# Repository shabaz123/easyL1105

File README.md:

# easyL1105 - What is it?
This repository contains resources for working with Texas Instruments MSPM0 microcontrollers, and in particular, the MSPM0L1105 microcontroller.
KiCad files, and Gerber files are present for building a simple development board, called easyL1105. 

The repository also contains Gerber files for a smaller miniL1105 board:

There is also an example starter project, which can be built with Keil or GCC.

# Circuit Diagrams
## easyL1105

## miniL1105

## Note for old Rev 1 Boards
The Rev 1 boards had a known bug; they were missing a 47k pull-up resistor from the *RST pin (pin 6 on the microcontroller) to +3.3V. The newer Rev 2 boards do not have this issue.

If you have a Rev 1 board, the fix is easy, it is possible to patch a resistor onto the underside of the PCB, using an 0805 sized resistor and a short length of 30 AWG Kynar wire.

The easyL1105 Rev 1 board allocates pins PA17(TXD) and PA18(RXD) for UART0, but since PA18(RXD) also has a BOOT function for enabling bootloader mode, there is the unfortunate situation that if the "BSL/UART0" board jumpers are configured to direct UART0 to the USB-UART chip, the pin is in BOOT mode during reset. One workaround for now is to not fit the rightmost jumper (rightmost when the "EasyL1105" and "BSL/UART0" text is the correct way up) during board reboot or power-up, and then fit it later. The better fix is in Rev 2, where a different GPIO pin (PA9) is used in place of PA18(RXD), so that it doesn't clash with the BOOT function

# easyL1105 Parts List
NOTE: The parts lists in this repository are for the Rev 1 board. They need to be updated for Rev 2. However, it is easy to read off the schematic what parts are required. 

| REF                | QTY | VALUE             | DESCRIPTION                                       |
| ------------------ | --- | ----------------- | ------------------------------------------------- |
| C1                 | 1   | 0.47u             | Tant Cap Case A example: T491A474M025AT           |
| C2, C5             | 2   | 10n               | 0805 MLCC Capacitor                               |
| C3,C6,C7           | 3   | 100n              | 0805 MLCC Capacitor                               |
| C4,C8,C9           | 3   | 10u 16V           | Tant Cap Case B example: TAJB106K016RNJ           |
| D1                 | 1   | GREEN             | LED GREEN 0603                                    |
| D2                 | 1   | BLUE              | LED BLUE 0603                                     |
| D3                 | 1   | 1N4001W           | Diode SOD-123                                     |
| D4                 | 1   | PWR               | LED RED 0603                                      |
| J1, J2, J5, J6, J7 | 1   | Header SIL        | Pin Header 2.54mm SIL 40-way (snapped to fit)     |
| J3                 | 1   | 2x5 DIL           | Pin Header 2.54mm DIL 10-way (2x5 way)            |
| J4                 | 1   | USB4085           | Socket GCT USB4805 / XUNPU USB-B10-BRW            |
| R1                 | 1   | 100k 0.1%         | 0805 Resistor 0.1%                                |
| R2,R3,R12          | 3   | 100R              | 0805 Resistor                                     |
| R4,R5,R7           | 3   | 100k              | 0805 Resistor                                     |
| R8,R9,R16          | 3   | 10k               | 0805 Resistor                                     |
| R10                | 1   | 220R              | 0805 Resistor                                     |
| R11                | 1   | 820R              | 0805 Resistor                                     |
| R19                | 1   | 1k                | 0805 Resistor                                     |
| R13                | 1   | 1M                | 0805 Resistor                                     |
| R14,R15            | 2   | 5.1k              | 0805 Resistor                                     |
| SW1, 2, 3          | 3   | Tact Switch       | Tact Button 4x3mm GCT SWT0110                     |
| U1                 | 1   | MSPM0L1105TDGS28R | TI MSPM0 L1105 VSSOP28 DGS                        |
| U2                 | 1   | CH340K            | WCH USB UART IC SSOP-10-1EP                       |
| U3                 | 1   | SRV05-4           | ESD Diode Array SOT23-6                           |
| U4                 | 1   | MIC5209-3.3YS     | LDO 3.3V SOT-223                                  |
| RFIX1              | 1   | 47k               | 0805 Resistor, patched between \*RST and 3.3V     |
| n/a                | 5   | Shorting Jumpers  | Jumpers 2-pin 2.54mm (Red, Black, Green x2, Blue) |

# Example Project
Go into the [**MyStarterProject**](https://github.com/shabaz123/easyL1105/tree/main/MyStarterProject) folder to see an example project called **app_L1105** (and if you plan to use GCC on Linux, then you need the **set_env.sh** file that is also in the MyStarterProject folder; save it to any convenient location). 

Go into the [**app_L1105**](https://github.com/shabaz123/easyL1105/tree/main/MyStarterProject/app_L1105) folder within MyStarterProject, and you'll find README notes explaining how to set up your PC and how to build the code.

If you were creating your own app based on the starter code, then rename the folder MyStarterProject to whatever name you want (for instance, MyLEDProject), and within there, retain the app_L1105 folder name (otherwise, you'd have to modify the contents of IDE files or makefiles). Then, edit the main.c file to do whatever you wish.

# Uploading your Application Firmware to the Microcontroller
Once you have built the example project, you'll want to upload it into the microcontroller. The easyL1105 board has a built-in USB-to-UART adapter. The miniL1105 board will require an external 3.3V logic level USB-UART adapter.

## Set Board Jumpers and Plug into PC
If you're using the easyL1105 board, ensure that two jumpers (green in the photo below) are fitted to direct the USB-UART to **BSL**, and not to UART0. Ensure that the PWR and GND jumpers are fitted (red and black in the photo below).

Attach the board using the USB cable to your PC, and check what port number is associated with it (for example, it may be a number like COM7 if you're using a Windows PC). If you don't see any port, then there may be a fault with the USB-UART circuitry, or an issue with the USB cable perhaps.

## Install and Run UniFlash
Download and install TI UniFlash. Run it, and at the top-right, set **Setting:Manual**. Next, under **Device**, click on **Category:MSP** and then type **MSPM0L110x** and you'll see a selection titled **MSPM0L110X(BOOTLOADER) Serial**. Click to select that.

Next, click on **Start**. 

You'll see a set of boxes appear. Click the empty text entry box to the right of **Application Image 1** and in the file browser that appears, browse to your built firmware file, which will have a **.hex** suffix, for instance, **app_L1105.hex**.

**Don't** press the Load Image button that appears just yet!

Instead, scroll further down, and you'll see a random COM port selected. In that box, type the correct COM port.

## Set Board to Bootloader Mode
Hold down the **BOOT** button on the board, press and release the **RESET** button, then release the **BOOT** button.

## Upload the Firmware
Now you can go back to the **Load Image** button in UniFlash, and press it.

Initially it may take a few seconds (or longer), but eventually you should see output like the following:

```
[21/08/2025, 23:56:17] [INFO] CORTEX_M0P: MSPM0L110x(Bootloader)
[21/08/2025, 23:56:17] [INFO] CORTEX_M0P: Invoking Bootloader....
[21/08/2025, 23:56:18] [ERROR] CORTEX_M0P: Automatic Bootloader invocation failed with response....1
[21/08/2025, 23:56:18] [ERROR] CORTEX_M0P: Try manual Bootloader Invocation...
[21/08/2025, 23:56:19] [INFO] CORTEX_M0P:
[21/08/2025, 23:56:19] [INFO] CORTEX_M0P: BSL Connected
[21/08/2025, 23:56:19] [INFO] CORTEX_M0P: Command Interpreter version: [0x0100] Build ID: [0x0100] Application version: [0x00000000] Active Plugin Interface version: [0x0001] BSL Max buffer size: [0x06C0] BSL Buffer Start address: [0x20000160] BCR Config ID: [0x00000x0001] BSL Config ID [0x00000x0001]
[21/08/2025, 23:56:19] [INFO] CORTEX_M0P: [80] [01] [00] [19] [B2] [B8] [96] [49]
[21/08/2025, 23:56:19] [INFO] CORTEX_M0P: {00}{08} {19} {00} {31} {00} {01} {00} {01} {00} {00} {00} {00} {01} {00} {C0} {06} {60} {01} {00} {20} {01} {00} {00} {00} {01} {00} {00} {00} {49} {61} {57} {8C}
[21/08/2025, 23:56:19] [INFO] CORTEX_M0P: BSL Password is correct!
[21/08/2025, 23:56:19] [INFO] CORTEX_M0P: [80] [21] [00] [21] [FF] [FF] [FF] [FF] [FF] [FF] [FF] [FF] [FF] [FF] [FF] [FF] [FF] [FF] [FF] [FF] [FF] [FF] [FF] [FF] [FF] [FF] [FF] [FF] [FF] [FF] [FF] [FF] [FF] [FF] [FF] [FF] [02] [AA] [F0] [3D]
[21/08/2025, 23:56:19] [INFO] CORTEX_M0P: {00}{08} {02} {00} {3B} {00} {38} {02} {94} {82}
[21/08/2025, 23:56:19] [INFO] CORTEX_M0P: Erasing sectors containing DataBlock starting at 0x0 is successful!
[21/08/2025, 23:56:19] [INFO] CORTEX_M0P: [80] [09] [00] [23] [00] [00] [00] [00] [8F] [02] [00] [00] [34] [27] [34] [14]
[21/08/2025, 23:56:19] [INFO] CORTEX_M0P: {00}{08} {02} {00} {3B} {00} {38} {02} {94} {82}
[21/08/2025, 23:56:19] [INFO] CORTEX_M0P: Erasing memory time elapsed: 0.03107s
[21/08/2025, 23:56:20] [INFO] CORTEX_M0P: [80] [95] [02] [20] [00] [00] [00] [00] [00] [10] [00] [20] [4D] [01] [00] [00] [51] [01] [00] [00] [53] [01] [00] [00] [00] [00] [00] [00] [00] [00] [00] [00] [00] [00] [00] [00] [00] [00] [00] [00] [00] [00] [00] [00] [00] [00] [00] [00] [00] [00] [00] [00] [55] [01] [00] [00] [00] [00] [00] [00] [00] [00] [00] [00] [57] [01] [00] [00] [59] [01] [00] [00] [5B] [01] [00] [00] [5B] [01] [00] [00] [5B] [01] [00] [00] [00] [00] [00] [00] [5B] [01] [00] [00] [00] [00] [00] [00] [00] [00] [00] [00] [00] [00] [00] [00] [00] [00] [00] [00] [5B] [01] [00] [00] [00] [00] [00] [00] [00] [00] [00] [00] [00] [00] [00] [00] [5B] [01] [00] [00] [00] [00] [00] [00] [5B] [01] [00] [00] [5B] [01] [00] [00] [00] [00] [00] [00] [5B] [01] [00] [00] [00] [00] [00] [00] [5B] [01] [00] [00] [00] [00] [00] [00] [00] [00] [00] [00] [00] [00] [00] [00] [5B] [01] [00] [00] [00] [00] [00] [00] [00] [00] [00] [00] [00] [00] [00] [00] [00] [00] [00] [00] [00] [00] [00] [00] [00] [00] [00] [00] [5B] [01] [00] [00] [00] [F0] [02] [F8] [00] [F0] [32] [F8] [0C] [A0] [30] [C8] [08] [38] [24] [18] [2D] [18] [67] [1E] [A2] [46] [AB] [46] [54] [46] [5D] [46] [AC] [42] [01] [D1] [00] [F0] [24] [F8] [7E] [46] [0F] [3E] [B6] [46] [0F] [CC] [01] [26] [33] [42] [00] [D0] [FB] [1A] [33] [43] [A2] [46] [AB] [46] [18] [47] [74] [01] [00] [00] [94] [01] [00] [00] [00] [00] [00] [00] [00] [23] [00] [24] [00] [25] [00] [26] [10] [3A] [01] [D3] [78] [C1] [FB] [D8] [52] [07] [00] [D3] [30] [C1] [00] [D5] [0B] [60] [70] [47] [1F] [B5] [1F] [BD] [10] [B5] [10] [BD] [00] [F0] [27] [F8] [11] [46] [FF] [F7] [F7] [FF] [00] [F0] [59] [F8] [00] [F0] [3F] [F8] [03] [B4] [FF] [F7] [F2] [FF] [03] [BC] [00] [F0] [45] [F8] [00] [00] [06] [48] [00] [47] [FE] [E7] [FE] [E7] [FE] [E7] [FE] [E7] [FE] [E7] [FE] [E7] [03] [48] [04] [49] [02] [4A] [04] [4B] [70] [47] [00] [00] [C1] [00] [00] [00] [60] [00] [00] [20] [00] [10] [00] [20] [00] [0C] [00] [20] [70] [47] [70] [47] [70] [47] [75] [46] [00] [F0] [24] [F8] [AE] [46] [05] [00] [69] [46] [53] [46] [C0] [08] [C0] [00] [85] [46] [18] [B0] [20] [B5] [FF] [F7] [E1] [FF] [60] [BC] [B6] [46] [00] [26] [00] [27] [C0] [C5] [C0] [C5] [C0] [C5] [C0] [C5] [C0] [C5] [C0] [C5] [C0] [C5] [C0] [C5] [40] [3D] [49] [08] [49] [00] [8D] [46] [70] [47] [10] [B5] [04] [46] [C0] [46] [C0] [46] [20] [46] [FF] [F7] [BA] [FF] [10] [BD] [00] [48] [70] [47] [00] [00] [00] [20] [01] [49] [18] [20] [AB] [BE] [FE] [E7] [26] [00] [02] [00] [70] [47] [81] [1E] [09] [1F] [00] [BF] [FC] [D2] [70] [47] [82] [B0] [1A] [48] [1A] [49] [41] [60] [1A] [49] [01] [60] [10] [20] [FF] [F7] [F2] [FF] [19] [48] [81] [21] [01] [60] [01] [20] [80] [06] [17] [49] [08] [60] [08] [63] [7D] [22] [92] [01] [0B] [46] [20] [3B] [18] [60] [00] [23] [1C] [46] [02] [E0] [64] [1C] [64] [2C] [08] [D0] [00] [93] [00] [9D] [95] [42] [F8] [D2] [00] [BF] [00] [9D] [6D] [1C] [00] [95] [F7] [E7] [08] [60] [00] [23] [1C] [46] [02] [E0] [64] [1C] [64] [2C] [E6] [D0] [01] [93] [01] [9D] [95] [42] [F8] [D2] [00] [BF] [01] [9D] [6D] [1C] [01] [95] [F7] [E7] [C0] [46] [00] [08] [0A] [40] [03] [00] [00] [B1] [01] [00] [00] [26] [6C] [80] [42] [40] [A0] [12] [0A] [40] [00] [00] [00] [00] [90] [02] [00] [00] [00] [00] [00] [20] [60] [00] [00] [00] [08] [01] [00] [00] [90] [02] [00] [00] [00] [0C] [00] [20] [00] [04] [00] [00] [08] [01] [00] [00] [5D] [8C] [43] [C0]
[21/08/2025, 23:56:20] [INFO] CORTEX_M0P: {00}{08} {02} {00} {3B} {00} {38} {02} {94} {82}
[21/08/2025, 23:56:20] [INFO] CORTEX_M0P: Programming memory time elapsed: 0.7061s
[21/08/2025, 23:56:20] [INFO] CORTEX_M0P: Number of bytes programmed: 656 bytes
[21/08/2025, 23:56:20] [INFO] CORTEX_M0P: Programming speed: 0.9073kByte/s
[21/08/2025, 23:56:20] [ERROR] CORTEX_M0P: Data Block Size less than 1KB!!! Verification Failed for Datablock at0x0
[21/08/2025, 23:56:20] [INFO] CORTEX_M0P: Verifying memory time elapsed: 0s
[21/08/2025, 23:56:20] [INFO] CORTEX_M0P: System Reset Issued!!!
[21/08/2025, 23:56:20] [INFO] CORTEX_M0P: System reset is executed!
[21/08/2025, 23:56:20] [INFO] CORTEX_M0P: [80] [01] [00] [40] [E2] [51] [21] [5B]
```

UniFlash may also report an error but still work (some versions of it are buggy like that) and if it went well, your board should immediately begin execution of the firmware, and flash LEDs if you're using the MyStarterProject app_L1105 on the easyL1105 board.

If UniFlash output doesn't look similar to that shown above, repeat the steps starting from the **Set Board to Bootloader Mode** section, in case it's a UniFlash issue.

# Non-UniFlash Option: Python Programmer
If you wish to use Python to program the chip rather than UniFlash, then see [the MSPM0 Programmer Python](https://github.com/shabaz123/easyL1105/tree/main/mspm0_programmer/python) folder.

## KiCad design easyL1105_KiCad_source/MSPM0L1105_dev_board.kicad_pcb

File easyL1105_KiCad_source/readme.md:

KiCad project files for the easyL1105 Rev 2 board

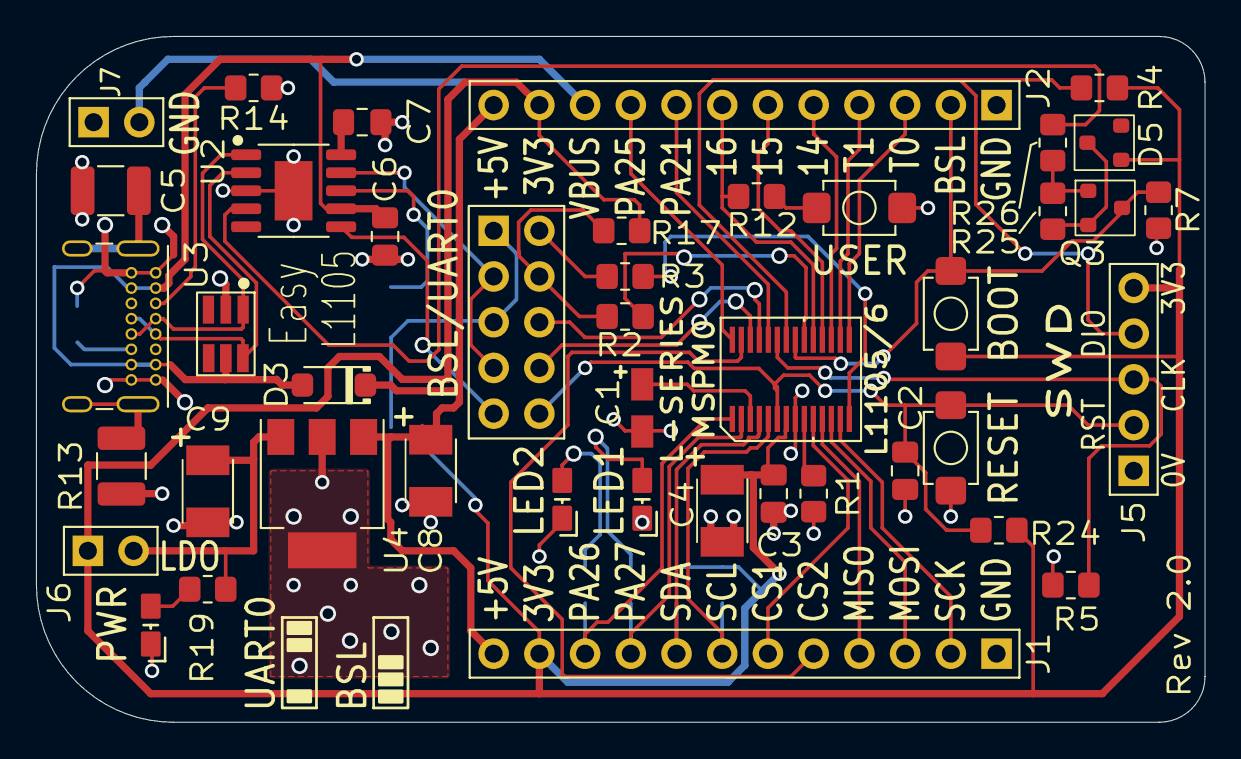
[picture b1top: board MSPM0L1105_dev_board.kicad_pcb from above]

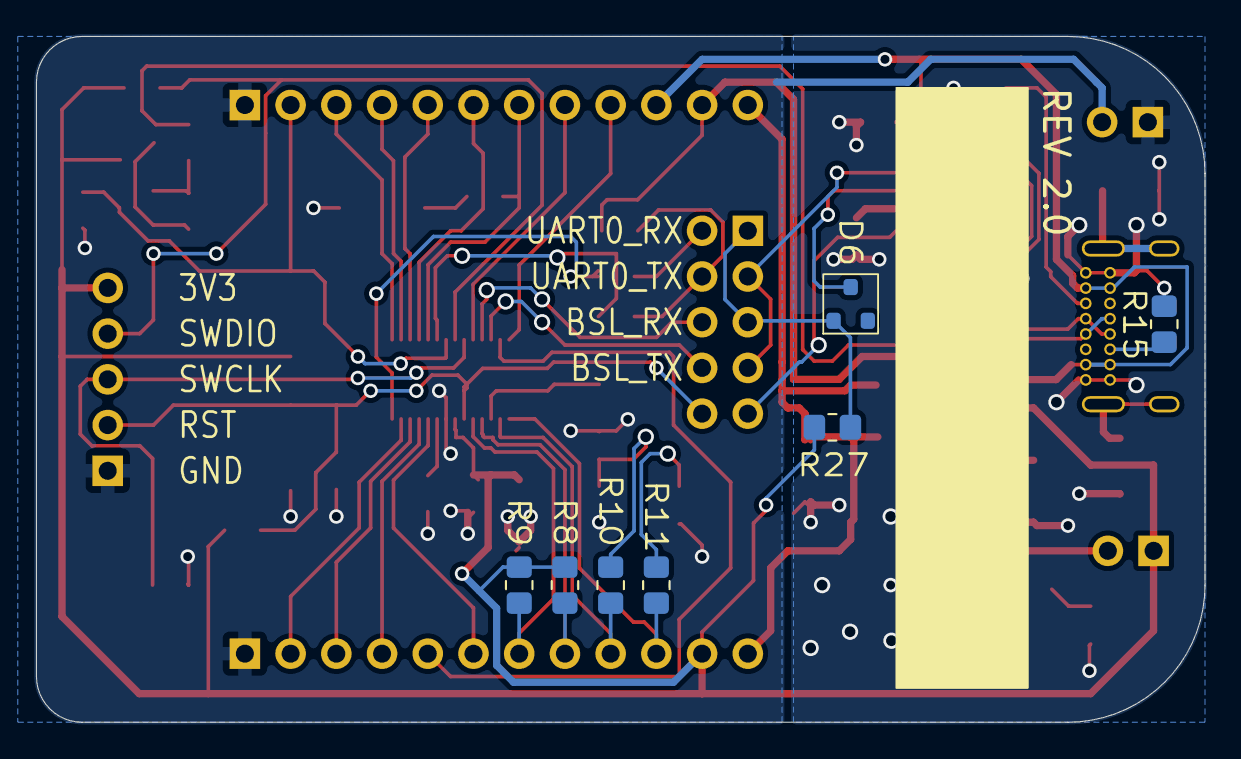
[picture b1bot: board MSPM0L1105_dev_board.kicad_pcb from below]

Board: 2 copper layers, 64.9 x 38.1 mm, 50 parts (7 on the bottom side), 52 nets.

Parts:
C1: 0.47u; Cap-Tant-T491A
C2: 10n; C_0805_2012Metric_Pad1.18x1.45mm_HandSolder
C3, C6, C7: 100n; C_0805_2012Metric_Pad1.18x1.45mm_HandSolder
C4, C8, C9: 10u; Cap-Tant-CaseB
C5: 10n; C_1210_3225Metric_Pad1.33x2.70mm_HandSolder
D1: GREEN; LED_0603_or_0805
D2: BLUE; LED_0603_or_0805
D3: 1N4001W; D_SOD-123-pins12
D4: RED; LED_0603_or_0805
D5, D6: BAS16; SOT-23-NEW
J1: IO_A; PinHeader_1x12_P2.54mm_Vertical
J2: IO_B; PinHeader_1x12_P2.54mm_Vertical
J3: UART-SELECT; PinHeader_2x5
J4: USB_C_Receptacle_USB4085; USB_C_Receptacle_GCT_USB4085_improved
J5: SWD; PinHeader_1x05_P2.54mm_Vertical
J6: LDO_JUMPER; PinHeader_1x02_P2.54mm_Vertical
J7: GND_JUMPER; PinHeader_1x02_P2.54mm_Vertical
Q3: BC857; SOT-23-NEW
R1: 100k 0.1%; R_0805_2012Metric_Pad1.20x1.40mm_HandSolder
R2, R3, R12: 100R; R_0805_2012Metric_Pad1.20x1.40mm_HandSolder
R4, R5, R7, R17: 100k; R_0805_2012Metric_Pad1.20x1.40mm_HandSolder
R8, R9, R25, R26, R27: 10k; R_0805_2012Metric_Pad1.20x1.40mm_HandSolder
R10: 220R; R_0805_2012Metric_Pad1.20x1.40mm_HandSolder
R11: 820R; R_0805_2012Metric_Pad1.20x1.40mm_HandSolder
R13: 1M; R_1210_3225Metric_Pad1.30x2.65mm_HandSolder
R14, R15: 5.1k; R_0805_2012Metric_Pad1.20x1.40mm_HandSolder
R19: 1k; R_0805_2012Metric_Pad1.20x1.40mm_HandSolder
R24: 47k; R_0805_2012Metric_Pad1.20x1.40mm_HandSolder
SW1: RESET; Tact-SW-4x3mm-body
SW2: BSL_BOOT; Tact-SW-4x3mm-body
SW3: USER_PA16; Tact-SW-4x3mm-body
U1: MSPM0L1105TDGS28R; VSSOP28-DGS-TI
U2: CH340K; SSOP-10-1EP_CH340K
U3: SRV05-4; SOT23-6
U4: MIC5209-3.3YS; SOT-223

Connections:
0V: C1.2, C2.2, C3.2, C4.2, D1.1 (K), D2.1 (K), J1.1, J2.1, J5.1, J7.2, R1.2, R5.2, R7.2, SW1.1, SW3.1, U1.8 (VSS)
+3.3V: C3.1, C4.1, D5.1 (A), J1.11, J2.11, J5.5, J6.1, R4.2, R8.1, R9.1, R17.1, R24.1, R27.1, SW2.2, U1.7 (VDD)
+5V: C8.1, D3.1 (K), J1.12, J2.12, U4.1 (IN)
/*DTR: R26.1, U2.4 (~DTR)
/*RST: C2.1, J3.10, J5.2, R24.2, SW1.2, U1.6 (*RST)
/BSL_INVOKE: J2.2, Q3.3 (C), R7.1, SW2.1, U1.21 (BSL_INVOKE/PA18)
/BSL_RX: J3.6, U1.25 (BSL_RX/PA22/A4)
/BSL_TX: J3.8, U1.26 (BSL_TX/VREF+/PA23)
/CS1: J1.6, U1.10 (CS1/PA3)
/CS2: J1.5, U1.27 (CS2/PA24/A3)
/MISO: J1.4, U1.11 (MISO/PA4)
/MOSI: J1.3, U1.12 (MOSI/PA5)
/PA9: R3.2, U1.14 (RXD/PA9)
/PA14: J2.5, U1.17 (PA14)
/PA15: J2.6, U1.18 (PA15/A9)
/PA16: J2.7, R12.2, U1.19 (PA16/A8)
/PA21: J2.8, U1.24 (VREF-/PA21/A5)
/PA25: J2.9, U1.28 (PA25/A2)
/PA26: J1.10, R11.1, U1.1 (PA26/A1)
/PA27: J1.9, R10.1, U1.2 (PA27/A0)
/RXD: D6.3 (K), U2.8 (TXD)
/SCK: J1.2, U1.13 (SCK/PA6)
/SCL: J1.7, R9.2, U1.5 (SCL/PA1)
/SDA: J1.8, R8.2, U1.4 (SDA/PA0)
/SWCLK: J5.3, R5.1, U1.23 (SWCLK/PA20/A6)
/SWDIO: J5.4, R4.1, U1.22 (SWDIO/PA19)
/TIMG4_C0: J2.3, U1.15 (TIMG4_C0/PA10)
/TIMG4_C1: J2.4, U1.16 (TIMG4_C1/PA11)
/TXD: J3.3, J3.7, U2.9 (RXD)
/UART0_RXD: J3.2, R3.1
/UART0_TXD: J3.4, R2.1, R17.2
Earth: C5.2, C6.1, C7.2, C8.2, C9.2, D4.1 (K), J4.A1 (GND), J4.A12 (GND), J4.B1 (GND), J4.B12 (GND), J7.1, R13.2, R14.2, R15.2, U2.3 (GND), U2.11 (GND), U3.2 (VN), U4.2 (GND)
unnamed: C5.1, J4.S1 (SHIELD)
unnamed: D1.2 (A), R10.2
unnamed: D2.2 (A), R11.2
unnamed: D4.2 (A), R19.2
unnamed: D5.3 (K), Q3.2 (E), R25.1
unnamed: D6.1 (A), J3.1, J3.5, R27.2
unnamed: J3.9, U2.6 (~RTS)
unnamed: J4.A5 (CC1), R14.1
unnamed: J4.B5 (CC2), R15.1
unnamed: J4.S2 (SHIELD), R13.1
unnamed: C9.1, J6.2, R19.1, U4.3 (OUT)
unnamed: Q3.1 (B), R25.2, R26.2
unnamed: R12.1, SW3.2
unnamed: R1.1, U1.9 (ROSC/PA2)
unnamed: R2.2, U1.20 (TXD/PA17)
unnamed: C1.1, U1.3 (VCORE)
unnamed: J4.A6 (D+), J4.B6 (D+), U2.1 (D+), U3.1 (IO1)
unnamed: J4.A7 (D-), J4.B7 (D-), U2.2 (D-), U3.6 (IO4)
unnamed: C7.1, U2.10 (V3)
VBUS: C6.2, D3.2 (A), J2.10, J4.A4 (VBUS), J4.A9 (VBUS), J4.B4 (VBUS), J4.B9 (VBUS), U2.7 (VCC), U3.5 (VP)

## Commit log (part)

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2025-08-22 Document known bug and fix for easyL1105 boards
    Added note about known bug and fix for easyL1105 boards.
2025-08-22 Update project description to include 'Rev 1'
2025-08-23 Add circuit diagrams section to README
    Added circuit diagrams for easyL1105 and miniL1105 boards.
2025-08-23 Enhance README with note and example project sections
    Updated section headers and added example project details.
2025-08-23 Clarify path to example project in README
2025-08-23 Improve README clarity on UniFlash errors
    Clarify instructions regarding UniFlash behavior and formatting in README.
2025-08-24 Clarify steps to upload firmware in UniFlash
    Added instructions for selecting firmware file in UniFlash.
2025-08-24 Update README with link to MyStarterProject
2025-08-24 Update README with clearer project setup instructions
2025-08-26 Fix image paths in README.md
    Updated image paths in README for clarity.
2025-08-26 Fix typo in SysConfig installation instructions
2025-09-05 Include Python Programmer option in README
2025-09-06 jancumps: removed the imports.mak[.OS_name]
    Fix from @jancumps, it cleans up the imports.mak which was causing issues for those that install the SDK via CCS, because that SDK is bundled slightly differently and does not include an imports.mak 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
2025-09-06 Add parts list for easyL1105 board
    Added a detailed parts list for the easyL1105 board, including component references, quantities, values, and descriptions.
2025-09-27 Flash erase command corrected to use end address, not length
2026-05-25 Revise README with introduction and setup details
    Updated README to include an introduction section and clarified project setup instructions.
2026-05-25 Fix link to set_env.sh in README
    Updated the link to set_env.sh in the README.
2026-05-26 Rev 2.0
2026-05-26 Update readme for easyL1105 to Rev 2
2026-05-26 Make schematic images clickable in main README
    Agent-Logs-Url: https://github.com/shabaz123/easyL1105/sessions/3d091ee9-08be-49fd-95bf-b4872f04906b
2026-05-26 Fix image links in README for circuit diagrams
    Updated the README to use proper HTML anchor tags for circuit diagram images.
2026-06-01 Update README with build instructions and SysConfig usage
    Added instructions for building a Release version and using SysConfig.
2026-06-01 Fix typo in README for Release build command
